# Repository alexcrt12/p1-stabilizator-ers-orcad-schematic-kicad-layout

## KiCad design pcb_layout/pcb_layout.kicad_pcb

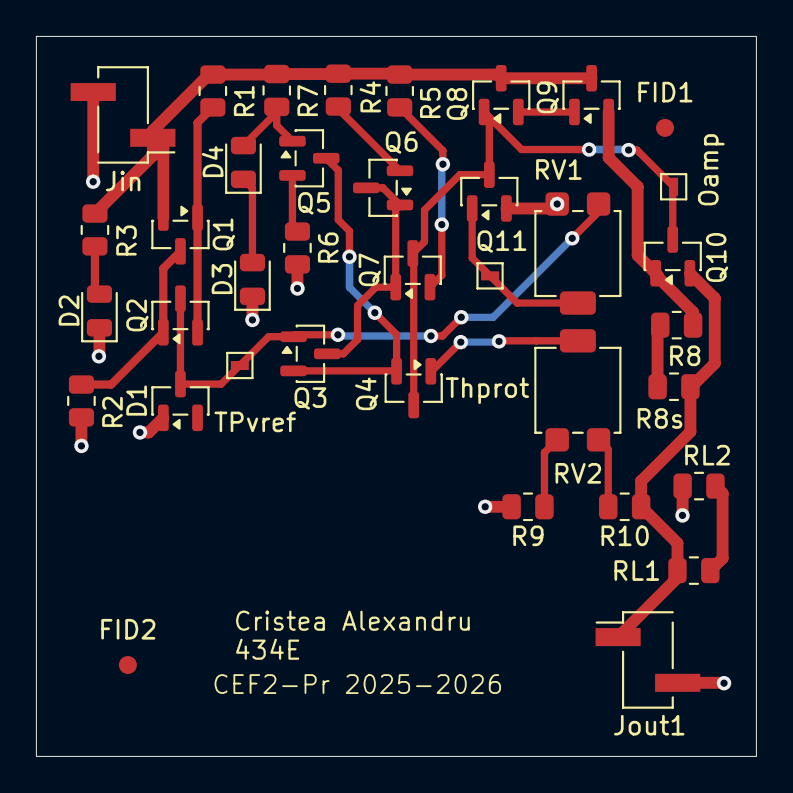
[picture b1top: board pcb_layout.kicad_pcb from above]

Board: 2 copper layers, 40.0 x 40.0 mm, 37 parts (0 on the bottom side), 23 nets.

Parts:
D1: BZX84C2V7; SOT-23
D2: LED; LED_0805_2012Metric
D3, D4: 1N4148; D_0805_2012Metric
FID1, FID2: Fiducial; Fiducial_1mm_Mask2mm
Jin: Conn_01x02_Pin; PinHeader_1x02_P2.54mm_Vertical_SMD_Pin1Left
Jout1: Conn_01x02_Pin; PinHeader_1x02_P2.54mm_Vertical_SMD_Pin1Left
Oamp: TestPoint; TestPoint_Pad_1.0x1.0mm
Q1, Q2, Q6, Q7: BC856; SOT-23
Q3, Q4, Q5, Q8, Q9: BC846; SOT-23
Q10, Q11: BC817; SOT-23
R1: 82; R_0805_2012Metric
R2, R4, R5, R7: 1k; R_0805_2012Metric
R3: 680; R_0805_2012Metric
R6: 220; R_0805_2012Metric
R8: 1; R_0805_2012Metric
R8s: 0.47; R_0805_2012Metric
R9: 2.7k; R_0805_2012Metric
R10: 1.8k; R_0805_2012Metric
RL1, RL2: 100; R_0805_2012Metric
RV1, RV2: 10k; Potentiometer_Bourns_3314G_Vertical
TPvref: TestPoint; TestPoint_Pad_1.0x1.0mm
Thprot: TestPoint; TestPoint_Pad_1.0x1.0mm

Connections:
/Vcc: Jin.1, Q1.2 (E), Q8.3 (C), Q9.3 (C), R1.1, R3.1, R4.1, R5.1, R7.1
/Vout: Jout1.1, Q10.2 (E), R8s.2, R10.1, RL1.1
GND: D1.1 (A), D2.1 (K), D3.1 (K), Jin.2, Jout1.2, Q11.2 (E), R2.2, R6.2, R9.2, RL2.2, RV1.3
unnamed: D1.3 (K), Q2.3 (C), Q3.1 (B), RV1.1, TPvref.1
unnamed: D2.2 (A), R3.2
unnamed: D3.2 (A), D4.1 (K)
unnamed: D4.2 (A), Q5.1 (B), R7.2
unnamed: Q1.1 (B), Q2.2 (E), R1.2
unnamed: Q1.3 (C), Q2.1 (B), R2.1
unnamed: Q3.3 (C), Q6.1 (B), Q6.3 (C), Q7.1 (B)
unnamed: Q3.2 (E), Q4.2 (E), Q5.3 (C)
unnamed: Q4.1 (B), RV2.2
unnamed: Q5.2 (E), R6.1
unnamed: Q6.2 (E), R4.2
unnamed: Q7.2 (E), R5.2
unnamed: Q8.2 (E), Q9.1 (B)
unnamed: Q9.2 (E), Q10.1 (B), R8.1
unnamed: Oamp.1, Q4.3 (C), Q7.3 (C), Q8.1 (B), Q10.3 (C), Q11.3 (C)
unnamed: Q11.1 (B), RV1.2, Thprot.1
unnamed: R8.2, R8s.1
unnamed: R9.1, RV2.1
unnamed: R10.2, RV2.3
unnamed: RL1.2, RL2.1
